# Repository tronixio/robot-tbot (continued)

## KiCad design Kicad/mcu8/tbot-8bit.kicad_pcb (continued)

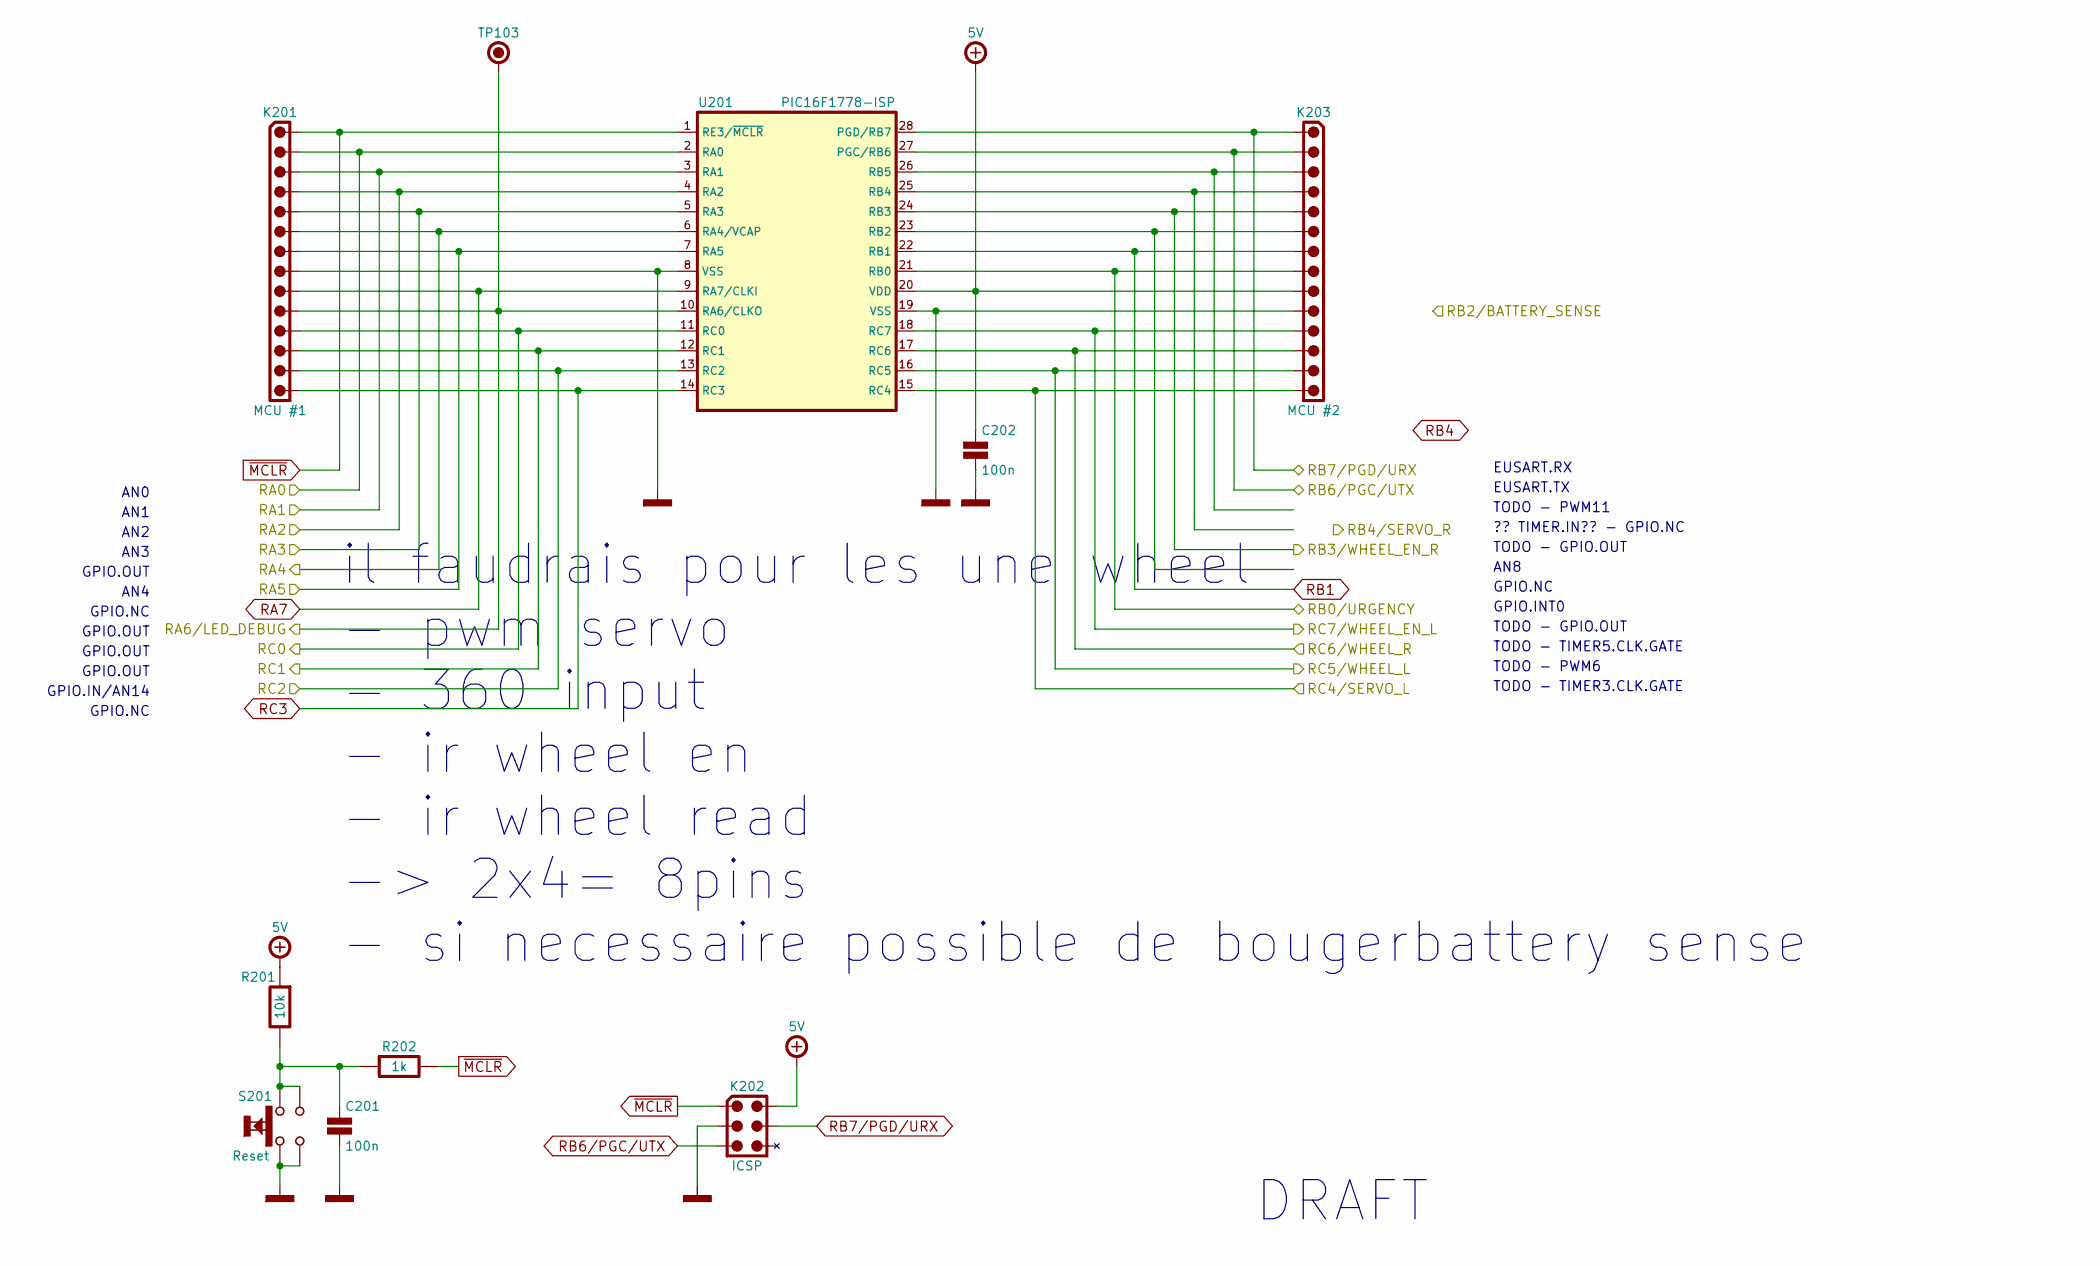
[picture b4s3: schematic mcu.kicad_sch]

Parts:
C201, C202: 100n; CAPACITOR-SMD-1206; Voltage 50V; Tolerance 5%; Mouser 80-C1206C104J5R
K201: MCU #1; HARWIN-M20-999144x; Mouser 855-M20-999144
K202: ICSP; HARWIN-M20-998034x; Mouser 855-M20-998034
K203: MCU #2; HARWIN-M20-999144x; Mouser 855-M20-999144
R201: 10k; RESISTOR-SMD-1206; Tolerance 5%; Mouser 660-RK73B2BTTDD103J
R202: 1k; RESISTOR-SMD-1206; Tolerance 5%; Mouser 660-RK73B2BTTDD102J
S201: Reset; ALPS-SKRPAC; Mouser 688-SKRPACE010
TP103: Debug; KEYSTONE-2000-3; Mouser 534-2000-3
U201: PIC16F1778-ISP; DIP-28-W762; Mouser 579-PIC16F1778-I/SP

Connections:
+5V: C202.1, K202.2, K203.9, R201.2, U201.20 (VDD); also elsewhere on the board
/HID/RA0: K201.2, U201.2 (RA0); also elsewhere on the board
/HID/RA1: K201.3, U201.3 (RA1); also elsewhere on the board
/HID/RA2: K201.4, U201.4 (RA2); also elsewhere on the board
/HID/RA3: K201.5, U201.5 (RA3); also elsewhere on the board
/HID/RA4: K201.6, U201.6 (RA4/VCAP); also elsewhere on the board
/HID/RA5: K201.7, U201.7 (RA5); also elsewhere on the board
/HID/RA6/LED_DEBUG: K201.10, U201.10 (RA6/CLKO); also elsewhere on the board
/HID/RB0/STOP: K203.8, U201.21 (RB0); also elsewhere on the board
/HID/RB3/WHEEL_EN_R: K203.5, U201.24 (RB3); also elsewhere on the board
/HID/RC0: K201.11, U201.11 (RC0); also elsewhere on the board
/HID/RC1: K201.12, U201.12 (RC1); also elsewhere on the board
/HID/RC2: K201.13, U201.13 (RC2); also elsewhere on the board
/HID/RC4/SERVO_L: K203.14, U201.15 (RC4); also elsewhere on the board
/HID/RC5/WHEEL_L: K203.13, U201.16 (RC5); also elsewhere on the board
/HID/RC6/WHEEL_R: K203.12, U201.17 (RC6); also elsewhere on the board
/HID/RC7/WHEEL_EN_L: K203.11, U201.18 (RC7); also elsewhere on the board
GND: C201.2, C202.2, K201.8, K202.3, K203.10, S201.1, S201.2, U201.8 (VSS), U201.19 (VSS); also elsewhere on the board
unnamed: C201.1, R201.1, R202.2, S201.3, S201.4
unnamed: K203.3, U201.26 (RB5)
unnamed: K203.4, U201.25 (RB4)
unnamed: K203.6, U201.23 (RB2)
RA7: K201.9, U201.9 (RA7/CLKI)
RB1: K203.7, U201.22 (RB1)
RB6/PGC/UTX: K202.5, K203.2, U201.27 (PGC/RB6); also elsewhere on the board
RB7/PGD/URX: K202.4, K203.1, U201.28 (PGD/RB7); also elsewhere on the board
RC3: K201.14, U201.14 (RC3)
~MCLR: K201.1, K202.1, R202.1, U201.1 (RE3/~MCLR)

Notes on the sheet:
AN2
AN8
AN1
GPIO.OUT
GPIO.NC
?? TIMER.IN?? - GPIO.NC
AN3
il faudrais pour les une wheel - pwm servo - 360 input - ir wheel en - ir wheel read -> 2x4= 8pins - si necessaire possible de bougerbattery sense
TODO - GPIO.OUT
AN4
TODO - PWM6
GPIO.IN/AN14
EUSART.TX
DRAFT
GPIO.INT0
TODO - TIMER3.CLK.GATE
TODO - TIMER5.CLK.GATE
TODO - PWM11
EUSART.RX
AN0

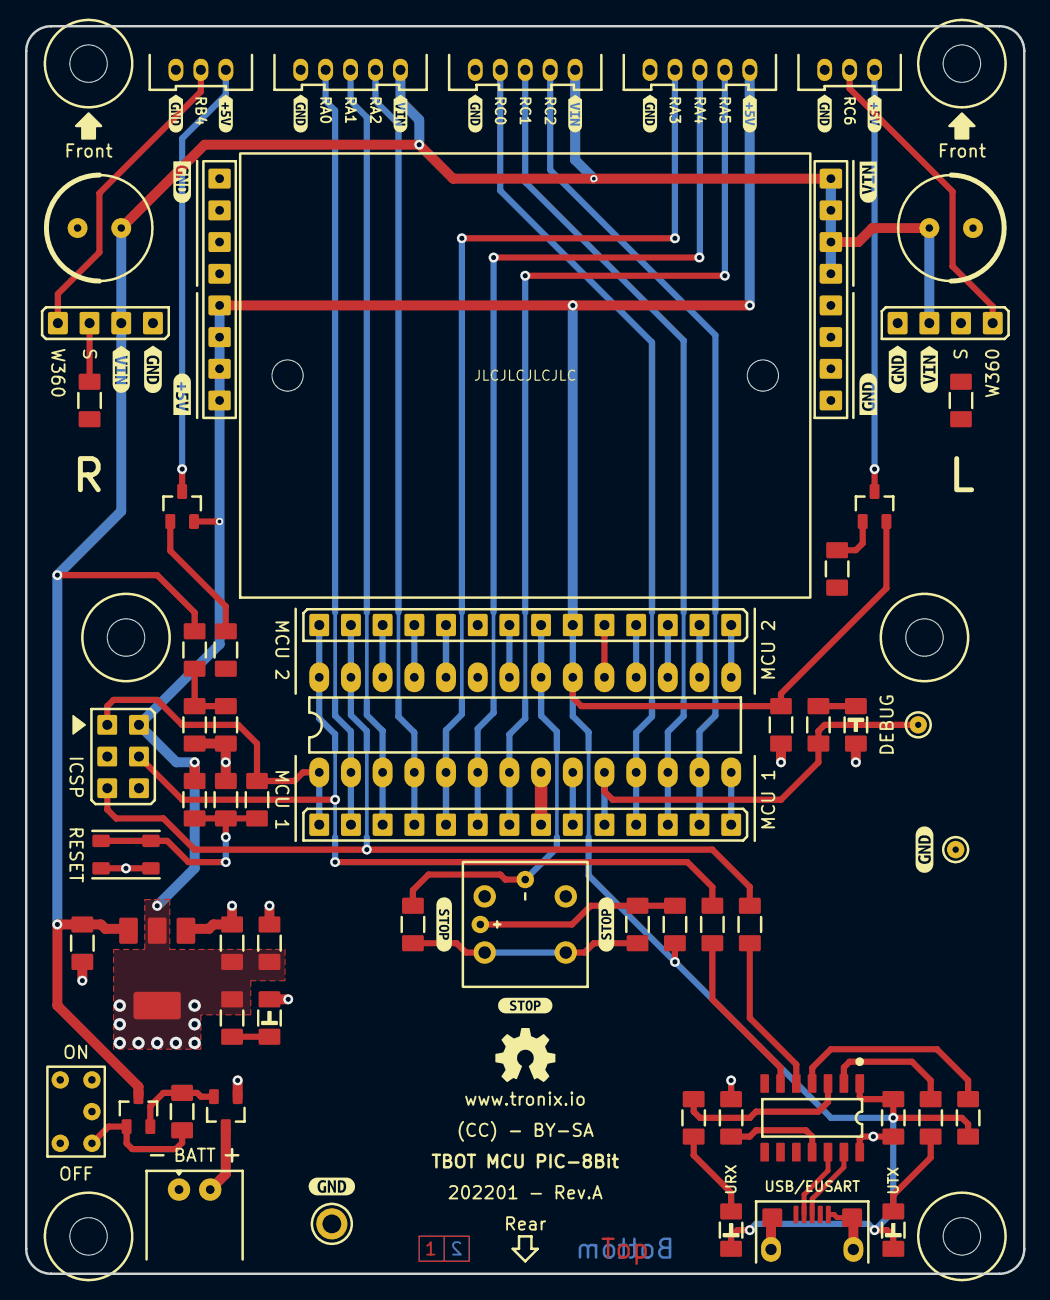
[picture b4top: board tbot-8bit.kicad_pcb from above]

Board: 2 copper layers, 80.0 x 100.0 mm, 90 parts (0 on the bottom side), 53 nets.

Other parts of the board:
TP201: Debug; KEYSTONE-2000-3
kibuzzard-627FC8D5: G***; kibuzzard-627FC8D5
kibuzzard-627FC68B: G***; kibuzzard-627FC68B
kibuzzard-627FC69F: G***; kibuzzard-627FC69F
kibuzzard-627FC691: G***; kibuzzard-627FC691
kibuzzard-627FC699: G***; kibuzzard-627FC699
kibuzzard-627FC905: G***; kibuzzard-627FC905
kibuzzard-627FC965: G***; kibuzzard-627FC965
kibuzzard-627FC987: G***; kibuzzard-627FC987
kibuzzard-6277F9C5: G001; kibuzzard-6277F9C5
kibuzzard-6567BC68, kibuzzard-6567BC68#2, kibuzzard-6567BC68#3: G***; kibuzzard-6567BC68
kibuzzard-62763CDA, kibuzzard-62763CDA#2, kibuzzard-62763CDA#4: G003; kibuzzard-62763CDA
kibuzzard-62763CDA#3: G005; kibuzzard-62763CDA
kibuzzard-62763D9F, kibuzzard-62763D9F#2: G004; kibuzzard-62763D9F
kibuzzard-62763D72: G002; kibuzzard-62763D72
kibuzzard-62763E7E: G010; kibuzzard-62763E7E
kibuzzard-62763E7E#2: G007; kibuzzard-62763E7E
kibuzzard-6294682B: G***; kibuzzard-6294682B
kibuzzard-62946869: G***; kibuzzard-62946869

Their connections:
/HID/RA6/LED_DEBUG: TP201.1; also elsewhere on the board

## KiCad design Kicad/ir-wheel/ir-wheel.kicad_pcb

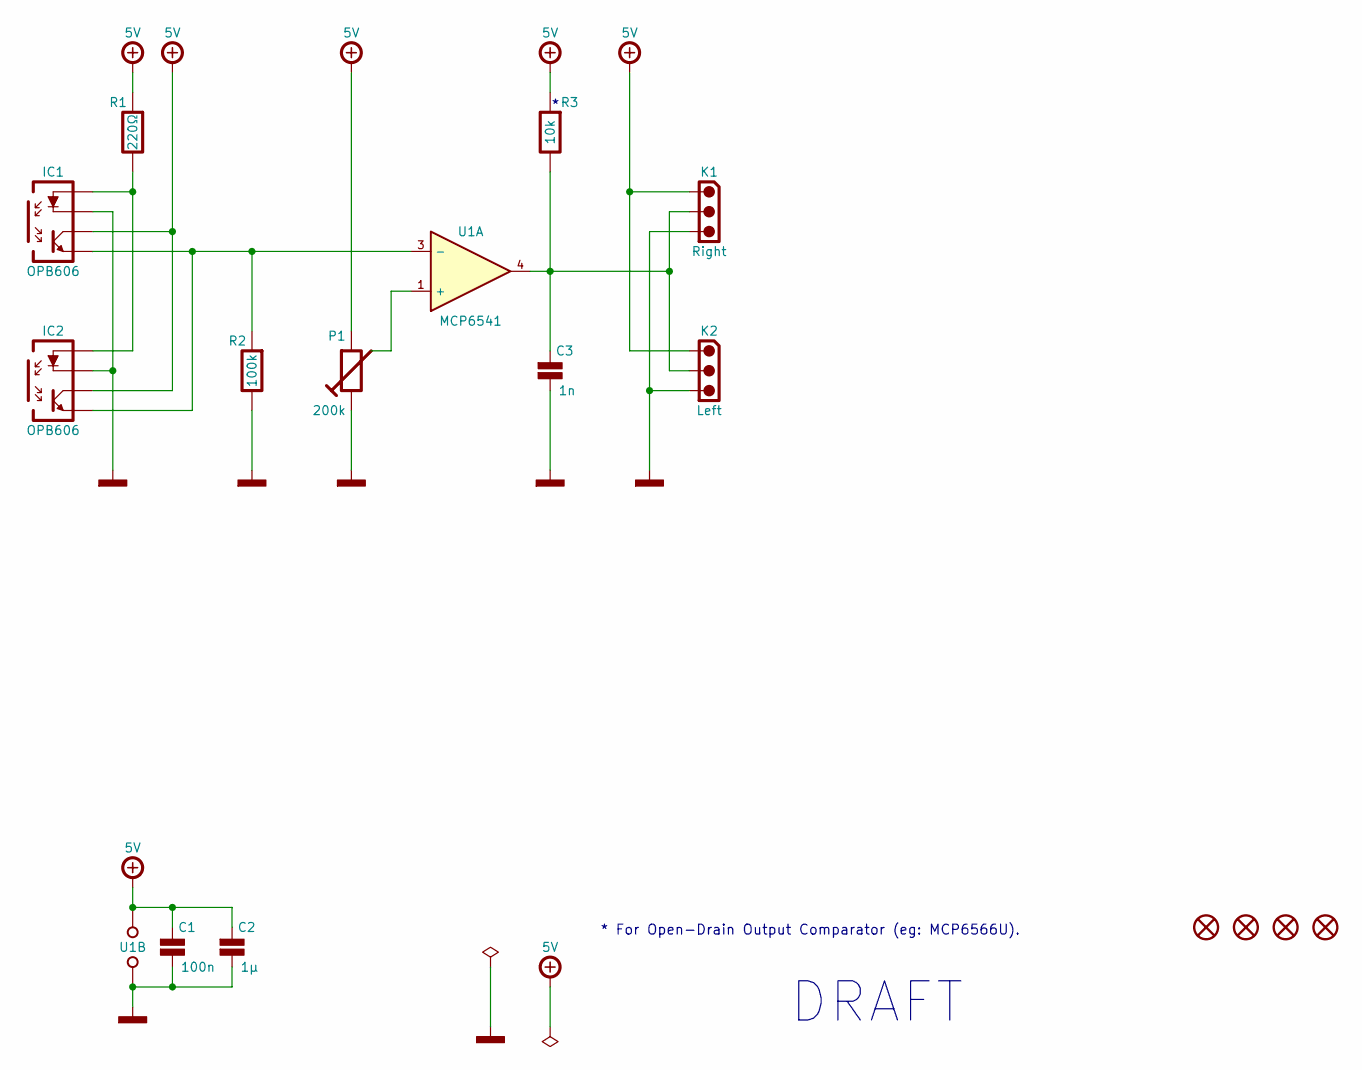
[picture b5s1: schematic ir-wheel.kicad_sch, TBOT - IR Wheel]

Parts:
C1: 100n; CAPACITOR-SMD-1206; Voltage 50V; Tolerance 10%; Mouser 187-CL31B106KAHNFNE
C2: 1µ; CAPACITOR-SMD-1206; Voltage 16V; Tolerance 10%; Mouser 80-C1206C105K4R
C3: 1n; CAPACITOR-SMD-1206; Voltage 50V; Tolerance 10%; Mouser 80-C1206C102K5R
H1, H2, H3, H4: MOUNTING-HOLE-3MM-MASK
IC1, IC2: OPB606; OPB-606; Mouser 828-OPB606
K1: Right; MOLEX-532540370; Mouser 538-53254-0370
K2: Left; MOLEX-532540370; Mouser 538-53254-0370
P1: 200k; TC33X; Mouser 652-TC33X-1-204E
R1: 220Ω; RESISTOR-SMD-1206; Tolerance 5%; Mouser 660-RK73B2BTTDD221J
R2: 100k; RESISTOR-SMD-1206; Tolerance 5%; Mouser 660-RK73B2BTTDD104J
R3: 10k; RESISTOR-SMD-1206; Tolerance 5%; Mouser 660-RK73B2BTTDD103J
U1: MCP6541; SOT-23-5; Mouser 579-MCP6541UT-E/OT

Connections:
+5V: C1.1, C2.1, IC1.3 (COLLECTOR), IC2.3 (COLLECTOR), K1.1, K2.1, P1.1, R1.2, R3.2, U1.5 (VDD)
GND: C1.2, C2.2, C3.2, IC1.2 (CATHODE), IC2.2 (CATHODE), K1.3, K2.3, P1.3, R2.1, U1.2 (VSS)
unnamed: C3.1, K1.2, K2.2, R3.1, U1.4
unnamed: IC1.1 (ANODE), IC2.1 (ANODE), R1.1
unnamed: IC1.4 (EMITTER), IC2.4 (EMITTER), R2.2, U1.3 (-)
unnamed: P1.2, U1.1 (+)

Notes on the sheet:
* For Open-Drain Output Comparator (eg: MCP6566U).
DRAFT

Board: 2 copper layers, 22 parts (5 on the bottom side), 6 nets, no tracks yet.

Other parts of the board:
GB: LOGO; OSHW-5MM
GT: LOGO; OSHW-5MM
kibuzzard-629B895E: G***; kibuzzard-629B895E
kibuzzard-629B896F: G***; kibuzzard-629B896F
kibuzzard-629B8952: G***; kibuzzard-629B8952
kibuzzard-629B8965: G***; kibuzzard-629B8965

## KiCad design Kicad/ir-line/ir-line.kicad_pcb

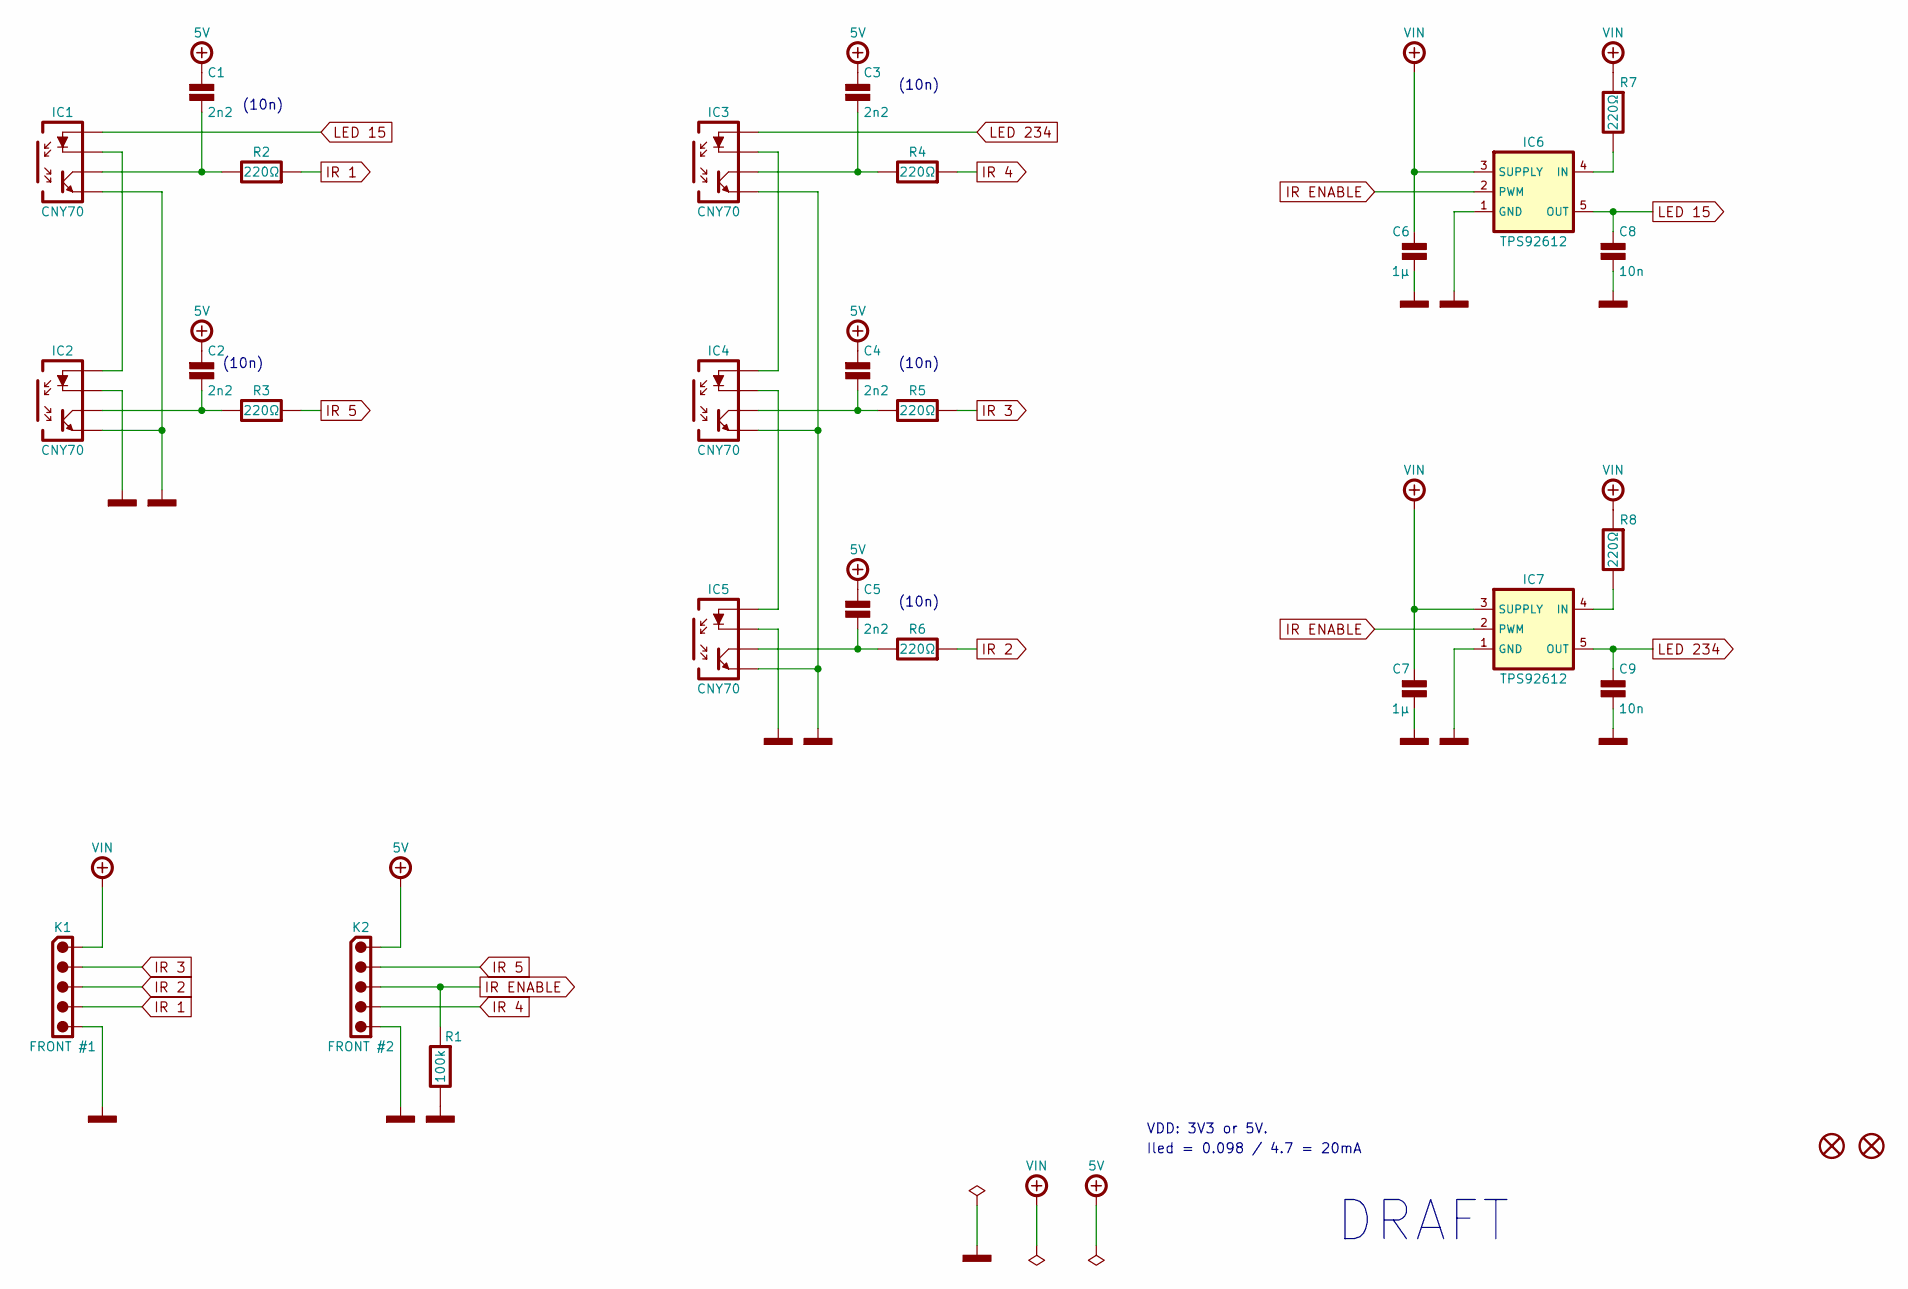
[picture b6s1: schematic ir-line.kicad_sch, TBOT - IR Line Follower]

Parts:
C1, C2, C3, C4, C5: 2n2; CAPACITOR-SMD-1206; Voltage 50V; Tolerance 10%; Mouser 80-C1206C222K5R
C6, C7: 1µ; CAPACITOR-SMD-1206; Voltage 16V; Tolerance 10%; Mouser 80-C1206C105K4R
C8, C9: 10n; CAPACITOR-SMD-1206; Voltage 50V; Tolerance 20%; Mouser 80-C1206C103M5R
H1, H2: MOUNTING-HOLE-3MM-MASK
IC1, IC2, IC3, IC4, IC5: CNY70; VISHAY-CNY70; Mouser 782-CNY70
IC6, IC7: TPS92612; SOT-23-5; Mouser 595-TPS92612DBVR
K1: FRONT #1; MOLEX-532530570; Mouser 538-53253-0570
K2: FRONT #2; MOLEX-532530570; Mouser 538-53253-0570
R1: 100k; RESISTOR-SMD-1206; Tolerance 5%; Mouser 660-RK73B2BTTDD104J
R2, R3, R4, R5, R6, R7, R8: 220Ω; RESISTOR-SMD-1206; Tolerance 5%; Mouser 660-RK73B2BTTDD221J

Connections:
+5V: C1.1, C2.1, C3.1, C4.1, C5.1, K2.1
GND: C6.2, C7.2, C8.2, C9.2, IC1.4 (EMITTER), IC2.2 (CATHODE), IC2.4 (EMITTER), IC3.4 (EMITTER), IC4.4 (EMITTER), IC5.2 (CATHODE), IC5.4 (EMITTER), IC6.1 (GND), IC7.1 (GND), K1.5, K2.5, R1.1
IR 1: K1.4, R2.2
IR 2: K1.3, R6.2
IR 3: K1.2, R5.2
IR 4: K2.4, R4.2
IR 5: K2.2, R3.2
IR ENABLE: IC6.2 (PWM), IC7.2 (PWM), K2.3, R1.2
LED 15: C8.1, IC1.1 (ANODE), IC6.5 (OUT)
LED 234: C9.1, IC3.1 (ANODE), IC7.5 (OUT)
unnamed: IC1.2 (CATHODE), IC2.1 (ANODE)
unnamed: C1.2, IC1.3 (COLLECTOR), R2.1
unnamed: C2.2, IC2.3 (COLLECTOR), R3.1
unnamed: IC3.2 (CATHODE), IC4.1 (ANODE)
unnamed: C3.2, IC3.3 (COLLECTOR), R4.1
unnamed: IC4.2 (CATHODE), IC5.1 (ANODE)
unnamed: C4.2, IC4.3 (COLLECTOR), R5.1
unnamed: C5.2, IC5.3 (COLLECTOR), R6.1
unnamed: IC6.4 (IN), R7.1
unnamed: IC7.4 (IN), R8.1
VIN: C6.1, C7.1, IC6.3 (SUPPLY), IC7.3 (SUPPLY), K1.1, R7.2, R8.2

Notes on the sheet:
(10n)
VDD: 3V3 or 5V.
DRAFT
Iled = 0.098 / 4.7 = 20mA

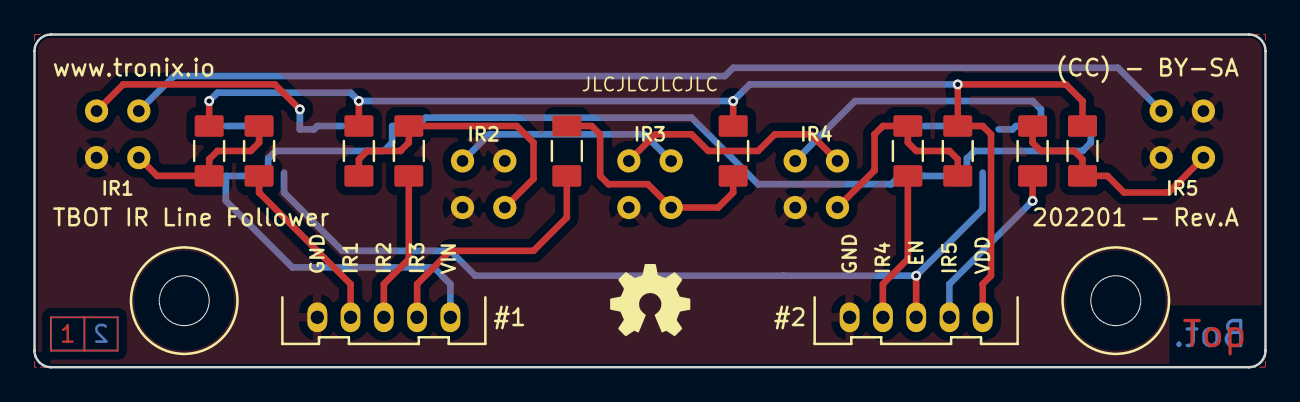
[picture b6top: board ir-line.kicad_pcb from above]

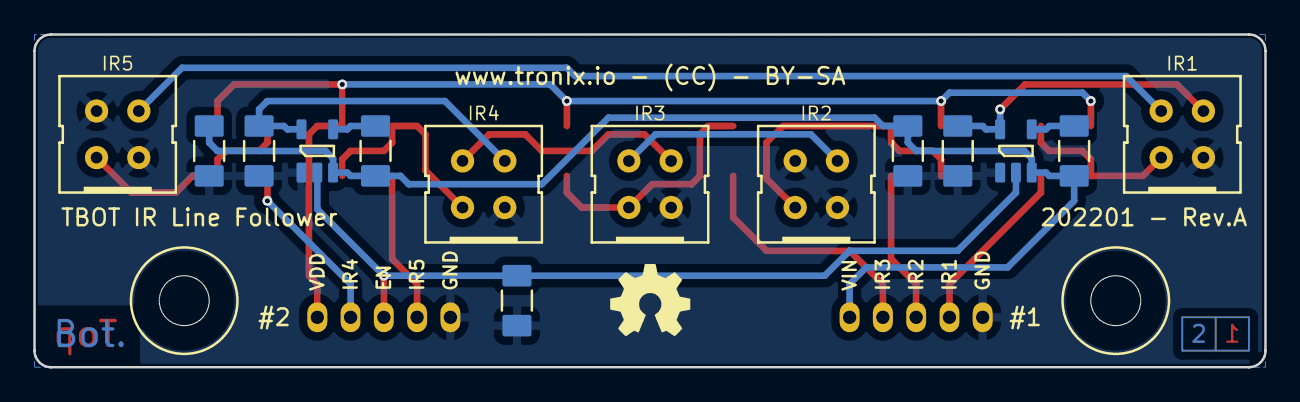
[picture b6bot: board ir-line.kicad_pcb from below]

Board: 2 copper layers, 74.0 x 20.0 mm, 30 parts (17 on the bottom side), 21 nets.

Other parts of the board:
GB: LOGO; OSHW-5MM
GT: LOGO; OSHW-5MM

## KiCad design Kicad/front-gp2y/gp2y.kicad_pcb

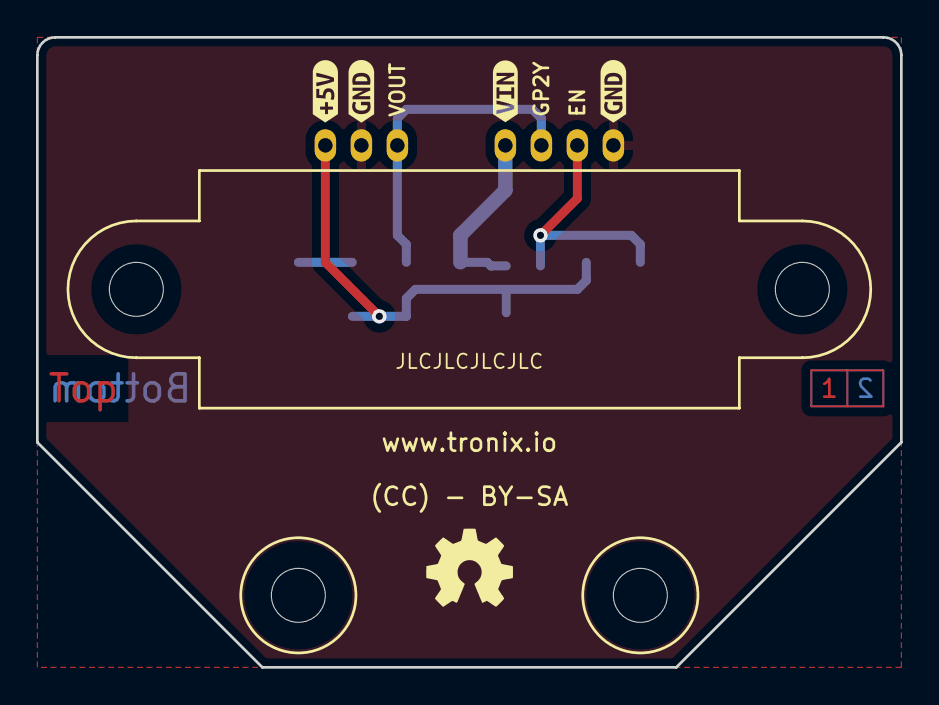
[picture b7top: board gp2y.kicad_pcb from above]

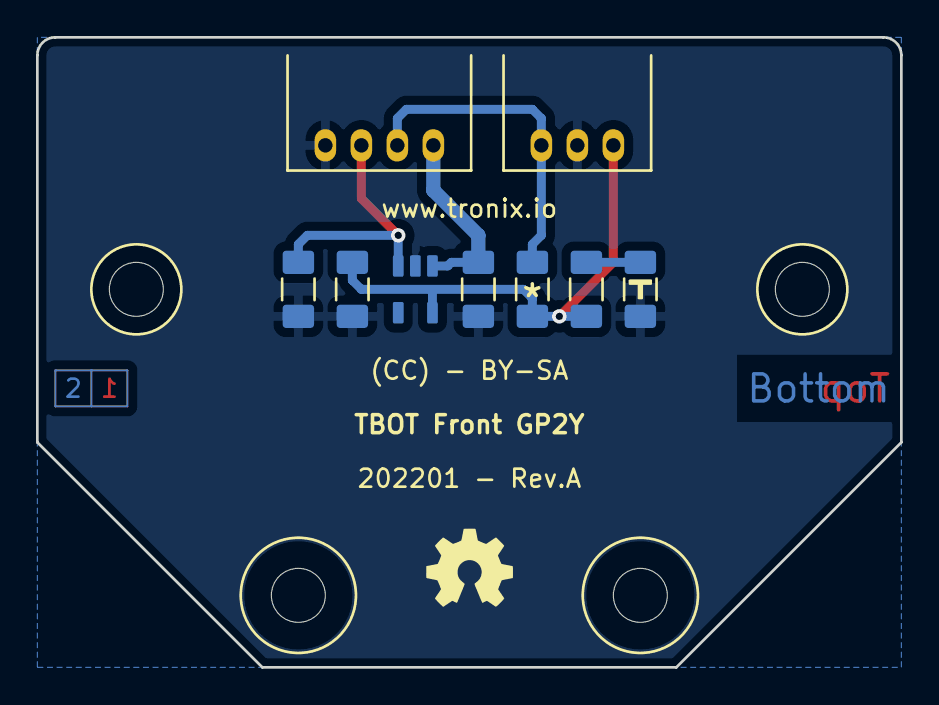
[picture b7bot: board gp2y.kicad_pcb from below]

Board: 2 copper layers, 48.0 x 35.0 mm, 18 parts (12 on the bottom side), 6 nets.

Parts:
C1, C2: 1µ; CAPACITOR-1206
GB: LOGO; OSHW-5MM
GT: LOGO; OSHW-5MM
H1, H2: MOUNTING-HOLE-MASK-3MM; M3-MASK
IC1: MCP1755-50; SOT-23-5
IR1: SHARP-GP2Y0xx1; SHARP-GP2Y0A
K1: GP2Y; MOLEX-532540370
K2: MCU; MOLEX-532540470
LED1: Power; LED-1206
R1: 100K; RESISTOR-1206
R2: 4K7; RESISTOR-1206
R3: 10K; RESISTOR-1206
kibuzzard-6277EDE4: G002; kibuzzard-6277EDE4
kibuzzard-6277EDE4#2: G004; kibuzzard-6277EDE4
kibuzzard-6277EE2E: G003; kibuzzard-6277EE2E
kibuzzard-6277EE50: G001; kibuzzard-6277EE50

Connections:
+5V: C2.1, IC1.5 (VOUT), K1.3, R2.1, R3.1
GND: C1.2, C2.2, IC1.2 (GND), K1.2, K2.1, LED1.1 (K), R1.2
GP2Y_OUT: K1.1, K2.3, R3.2
MCU_ENABLE: IC1.3 (~SHDN), K2.2, R1.1
unnamed: LED1.2 (A), R2.2
VIN: C1.1, IC1.1 (VIN), K2.4

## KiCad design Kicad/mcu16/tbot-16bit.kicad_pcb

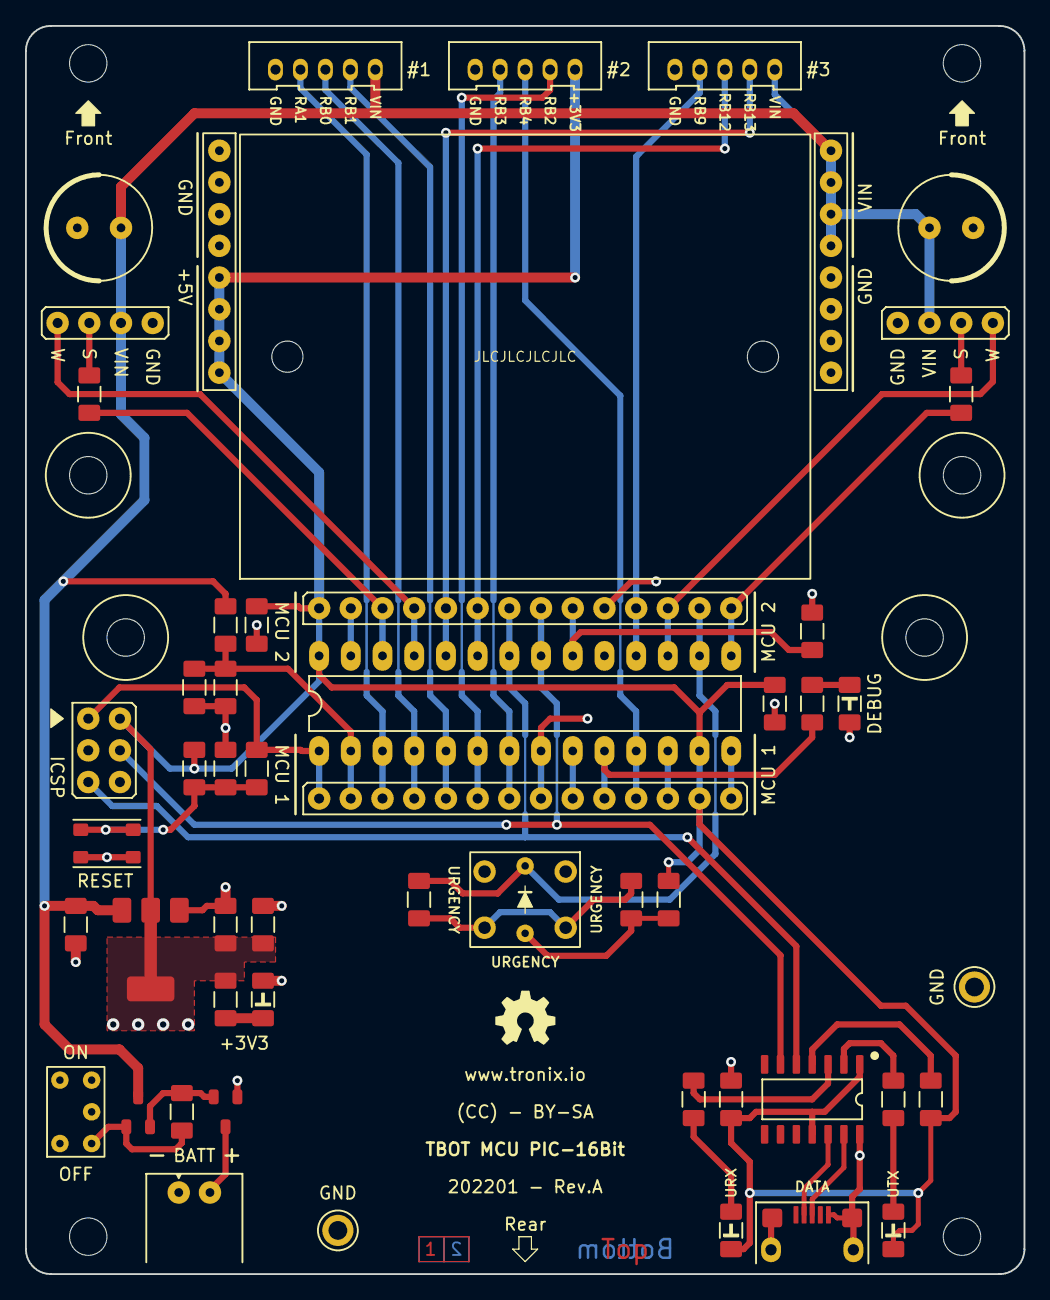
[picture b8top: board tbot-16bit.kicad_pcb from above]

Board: 2 copper layers, 80.0 x 100.0 mm, 61 parts (0 on the bottom side), 43 nets.

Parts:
BB401: BREADBOARD-170
C101, C103, C301, C302, C303, C402: 100n; CAPACITOR-1206
C102, C104, C304: 10µ; CAPACITOR-1206
C401, C404: 220µ/25V; CAPACITOR-ELECTROLYTIC-RADIAL-080-115-035
H101, H102, H103, H104, H105, H106: MOUNTING-HOLE-MASK-3MM; M3-MASK
H107, H108: MOUNTING-HOLE-3MM; M3
IC101: TLV1117-33-SOT; SOT-223-3
IC301: PIC24FJxxGA002-ISP; DIP-28-W762
IC401: MCP2221A; SOIC-SL-14
K101: Battery; MOLEX-22057025
K301: MCU 1; HARWIN-M20-999144x
K302: ICSP; HARWIN-M20-998034x
K303: MCU 2; HARWIN-M20-999144x
K401: FRONT #1; MOLEX-532530570
K402: FRONT #2; MOLEX-532530570
K403: VIN; HARWIN-M20-782084x
K404: +5V; HARWIN-M20-782084x
K405: FRONT #3; MOLEX-532530570
K406: SERVO LEFT; HARWIN-M20-999044x
K407: USB/UART; FCI-USB-TYPE-B-MICRO-THT
K408: SERVO RIGHT; HARWIN-M20-999044x
LED101: Power; LED-1206
LED401: Debug; LED-1206
LED402: URX; LED-1206
LED403: UTX; LED-1206
R101: 16K; RESISTOR-1206
R102: 1M; RESISTOR-1206
R103, R301, R407: 10K; RESISTOR-1206
R104, R404, R408, R410: 1K2; RESISTOR-1206
R302: 1K; RESISTOR-1206
R401, R406, R411: 220Ω; RESISTOR-1206
R402: 150Ω; RESISTOR-1206
R403: 330Ω; RESISTOR-1206
S101: Power; E-SWITCH-200USPXT1A1M2RE
S301: Reset; ALPS-SKRPAC
S401: EMERGENCY; E-SWITCH-TL1240XQ1JXXX
T101, T102: DMP2305U; SOT-23-3
TP101, TP102: GND; KEYSTONE-5006

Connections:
+3V3: C103.1, C104.1, C302.1, C303.1, C402.1, IC101.2 (VO), IC301.13 (VDD), IC301.28 (VDD), IC401.1 (VDD), IC401.11 (VUSB), K301.13, K302.2 (VDD), K303.1, K402.1, K404.1, K404.2, K404.3, K404.4, LED402.2 (A), LED403.2 (A), R104.2, R301.2, R401.2, R407.2
/HID/D+: IC401.13 (D+), K407.3 (D+)
/HID/D-: IC401.12 (D-), K407.2 (D-)
/HID/RA1: IC301.3 (RA1), K301.3, K401.4
/HID/RA3/LED: IC301.10 (RA3/CLKO), K301.10, R404.2
/HID/RB0: IC301.4 (RB0/PGD1), K301.4, K401.3
/HID/RB1: IC301.5 (RB1/PGC1), K301.5, K401.2
/HID/RB2: IC301.6 (RB2), K301.6, K402.2
/HID/RB3: IC301.7 (RB3), K301.7, K402.4
/HID/RB4: IC301.11 (RB4), K301.11, K402.3
/HID/RB6/SERVO_R: IC301.15 (RB6), K303.14, R411.1
/HID/RB7/EMERGENCY: IC301.16 (RB7), K303.13, R403.2, S401.5 (C)
/HID/RB8/WHEEL_R: IC301.17 (RB8), K303.12, K408.4
/HID/RB9: IC301.18 (RB9), K303.11, K405.4
/HID/RB10/PGD/URX: IC301.21 (RB10), IC401.6 (UTx), K302.4 (PGD), K303.8
/HID/RB11/PGC/UTX: IC301.22 (RB11), IC401.5 (URx), K302.5 (PGC), K303.7
/HID/RB12: IC301.23 (RB12), K303.6, K405.3
/HID/RB13: IC301.24 (RB13), K303.5, K405.2
/HID/RB14/WHEEL_L: IC301.25 (RB14), K303.4, K406.4
/HID/RB15/SERVO_L: IC301.26 (RB15), K303.3, R406.1
GND: C101.2, C102.2, C103.2, C104.2, C301.2, C302.2, C303.2, C304.2, C401.2, C402.2, C404.2, IC101.1 (GND), IC301.8 (VSS), IC301.19 (DISVREG), IC301.27 (VSS), IC401.14 (VSS), K101.1, K301.8, K302.3 (GND), K303.2, K303.10, K401.5, K402.5, K403.5, K403.6, K403.7, K403.8, K404.5, K404.6, K404.7, K404.8, K405.5, K406.1, K407.5 (GND), K407.6 (SHIELD), K408.1, LED101.1 (K), LED401.1 (K), R103.1, S101.2, S301.1, S301.2, S401.1, S401.2, T101.1 (G), TP101.1, TP102.1
unnamed: C301.1, R301.1, R302.2, S301.3, S301.4
unnamed: C304.1, IC301.20 (VCAP/VDDCORE), K303.9
unnamed: IC401.2 (GP0), R410.1
unnamed: IC401.3 (GP1), R408.1
unnamed: IC401.4 (~RESET), R407.1
unnamed: K406.3, R406.2
unnamed: K408.3, R411.2
unnamed: LED101.2 (A), R104.1
unnamed: LED401.2 (A), R404.1
unnamed: LED402.1 (K), R408.2
unnamed: LED403.1 (K), R410.2
unnamed: R102.1, S101.3, T102.1 (G)
unnamed: R102.2, T101.2 (S), T102.2 (S)
unnamed: R401.1, R402.2, S401.6 (A)
unnamed: R402.1, R403.1, S401.3, S401.4
RA0/BATTERY_SENSE: C101.1, IC301.2 (RA0), K301.2, R101.1, R103.2
RA2: IC301.9 (RA2/CLKI), K301.9
RA4: IC301.12 (RA4), K301.12
RB5: IC301.14 (RB5), K301.14
VBAT: K101.2, T101.3 (D)
VIN: C102.1, C401.1, C404.1, IC101.3 (VI), K401.1, K403.1, K403.2, K403.3, K403.4, K405.1, K406.2, K408.2, R101.2, T102.3 (D)
~MCLR: IC301.1 (~MCLR), K301.1, K302.1 (~MCLR), R302.1

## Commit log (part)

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2022-03-05 Update MCU 8Bit
2022-03-06 Create MCU 16Bits
2022-03-12 Draft
2022-03-12 Restore
2022-03-20 Update Charger
2022-03-20 Update MCU8
2022-03-20 Create IR Wheel
2022-03-20 Update GP2Y
2022-03-27 Update HC-SR04
2022-03-27 Update IR Line
2022-03-27 Update IR Wheel
2022-04-09 Delete
2022-04-27 Update MCU
2022-04-27 Update Code
2022-05-08 Update TX
2022-05-08 Update TX/RX
2022-05-08 Add IR Wheel
2022-05-08 Move PICS
2022-05-08 Update Code Configuration
2022-05-08 Update EUSART-TX
2022-05-08 Update EUSART TX/RX
2022-05-08 Update ADC
2022-05-08 Update Code PWM
2022-05-08 Update Code GP2Y
2022-05-08 Update Code INT0
2023-10-17 Up charger
2023-10-17 Up gp2y
2023-10-17 Up hc-sr04
2023-10-28 Delet
2024-09-20 Change gitignore
